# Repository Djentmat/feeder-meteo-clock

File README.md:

# feeder-meteo-clock
Arduino progect including siemens a70 lcd, BME280, RTC module, and servo feeder for a rat

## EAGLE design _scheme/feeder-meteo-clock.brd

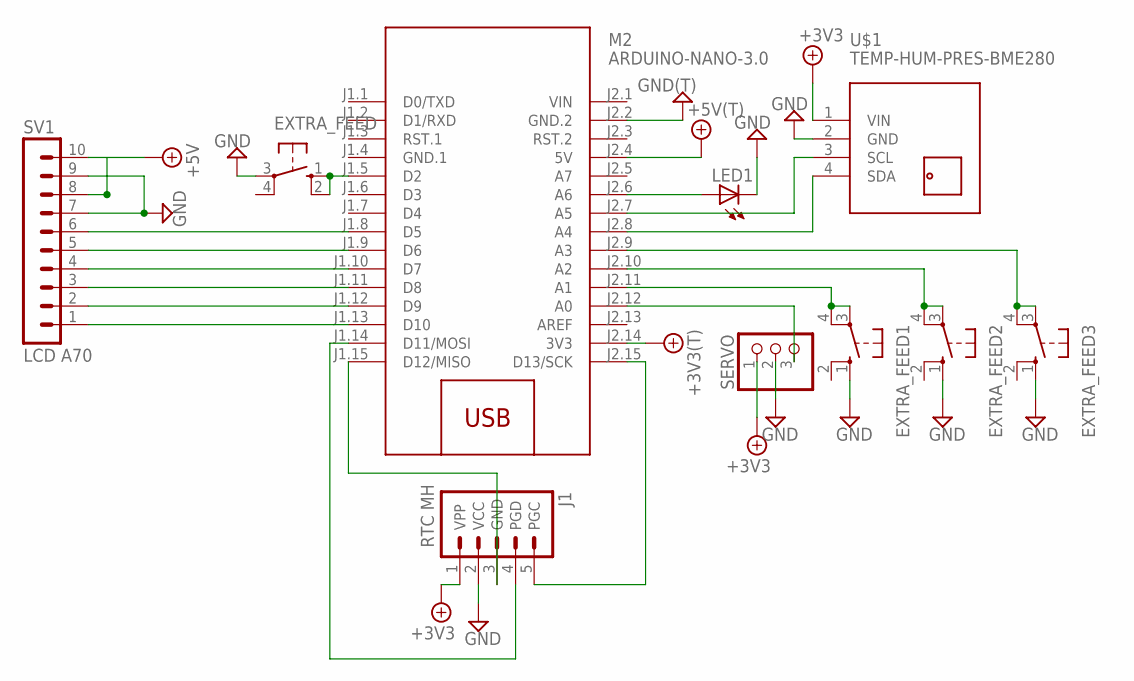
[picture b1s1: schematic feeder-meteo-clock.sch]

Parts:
+3V1: +3V3(T); SQUARE
+9V1: +5V(T); SQUARE
EXTRA_FEED, EXTRA_FEED1, EXTRA_FEED2, EXTRA_FEED3: 10-XX; B3F-10XX
GND1: GND(T); SQUARE
J1: RTC MH; PIC_ICSP_MINI_5_PIN
LED1: LED3MM
M2: ARDUINO-NANO-3.0
SERVO: PINHD-1X3; 1X03
SV1: LCD A70; MA10-1
U$1: TEMP-HUM-PRES-BME280

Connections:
+9V: +9V1.1, M2.J2.4 (5V), SV1.8, SV1.10
+18V: +3V1.1, J1.1 (VPP), M2.J2.14 (3V3), SERVO.1, U$1.1 (VIN)
GND: EXTRA_FEED.3, EXTRA_FEED1.1 (S), EXTRA_FEED2.1 (S), EXTRA_FEED3.1 (S), GND1.1, J1.2 (VCC), LED1.K (C), M2.J2.2 (GND.2), SERVO.2, SV1.7, SV1.9, U$1.2 (GND)
GND.1: M2.J1.4 (GND.1)
unnamed: M2.J2.8 (A4), U$1.4 (SDA)
unnamed: M2.J2.7 (A5), U$1.3 (SCL)
unnamed: EXTRA_FEED1.3, EXTRA_FEED1.4 (P1), M2.J2.11 (A1)
unnamed: J1.5 (PGC), M2.J2.15 (D13/SCK)
unnamed: EXTRA_FEED2.3, EXTRA_FEED2.4 (P1), M2.J2.10 (A2)
unnamed: EXTRA_FEED3.3, EXTRA_FEED3.4 (P1), M2.J2.9 (A3)
unnamed: J1.4 (PGD), M2.J1.14 (D11/MOSI)
unnamed: M2.J1.8 (D5), SV1.6
unnamed: M2.J1.9 (D6), SV1.5
unnamed: J1.3 (GND), M2.J1.15 (D12/MISO)
unnamed: LED1.A, M2.J2.6 (A6)
unnamed: M2.J2.12 (A0), SERVO.3
unnamed: EXTRA_FEED.1 (S), EXTRA_FEED.2 (S1), M2.J1.5 (D2)
unnamed: M2.J1.10 (D7), SV1.4
unnamed: M2.J1.11 (D8), SV1.3
unnamed: M2.J1.12 (D9), SV1.2
unnamed: M2.J1.13 (D10), SV1.1
VIN: M2.J2.1 (VIN)

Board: 2 copper layers, 13 parts (0 on the bottom side), 20 nets, no tracks yet.

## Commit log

2020-03-30 Added full main screen drawing
2020-04-18 1. Drawin pressure and temperature graph
2020-04-19 Done: Drawin pressure and temperature graph, settin up a main time, date, feed time and period. Redisigned a main screen
2020-04-21 Fixed approximation
2020-11-17 ===DEVICE WWAS CREATED=== DONE: Created schematic and make some bugfixes
2020-12-27 CONFIG: comment feed_time2

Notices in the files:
parts and their libraries:
diy-modules: Released under the Creative Commons Attribution 4.0 International License: http://creativecommons.org/licenses/by/4.0
SparkFun-Connectors: Licensing: Creative Commons ShareAlike 4.0 International - https://creativecommons.org/licenses/by-sa/4.0
